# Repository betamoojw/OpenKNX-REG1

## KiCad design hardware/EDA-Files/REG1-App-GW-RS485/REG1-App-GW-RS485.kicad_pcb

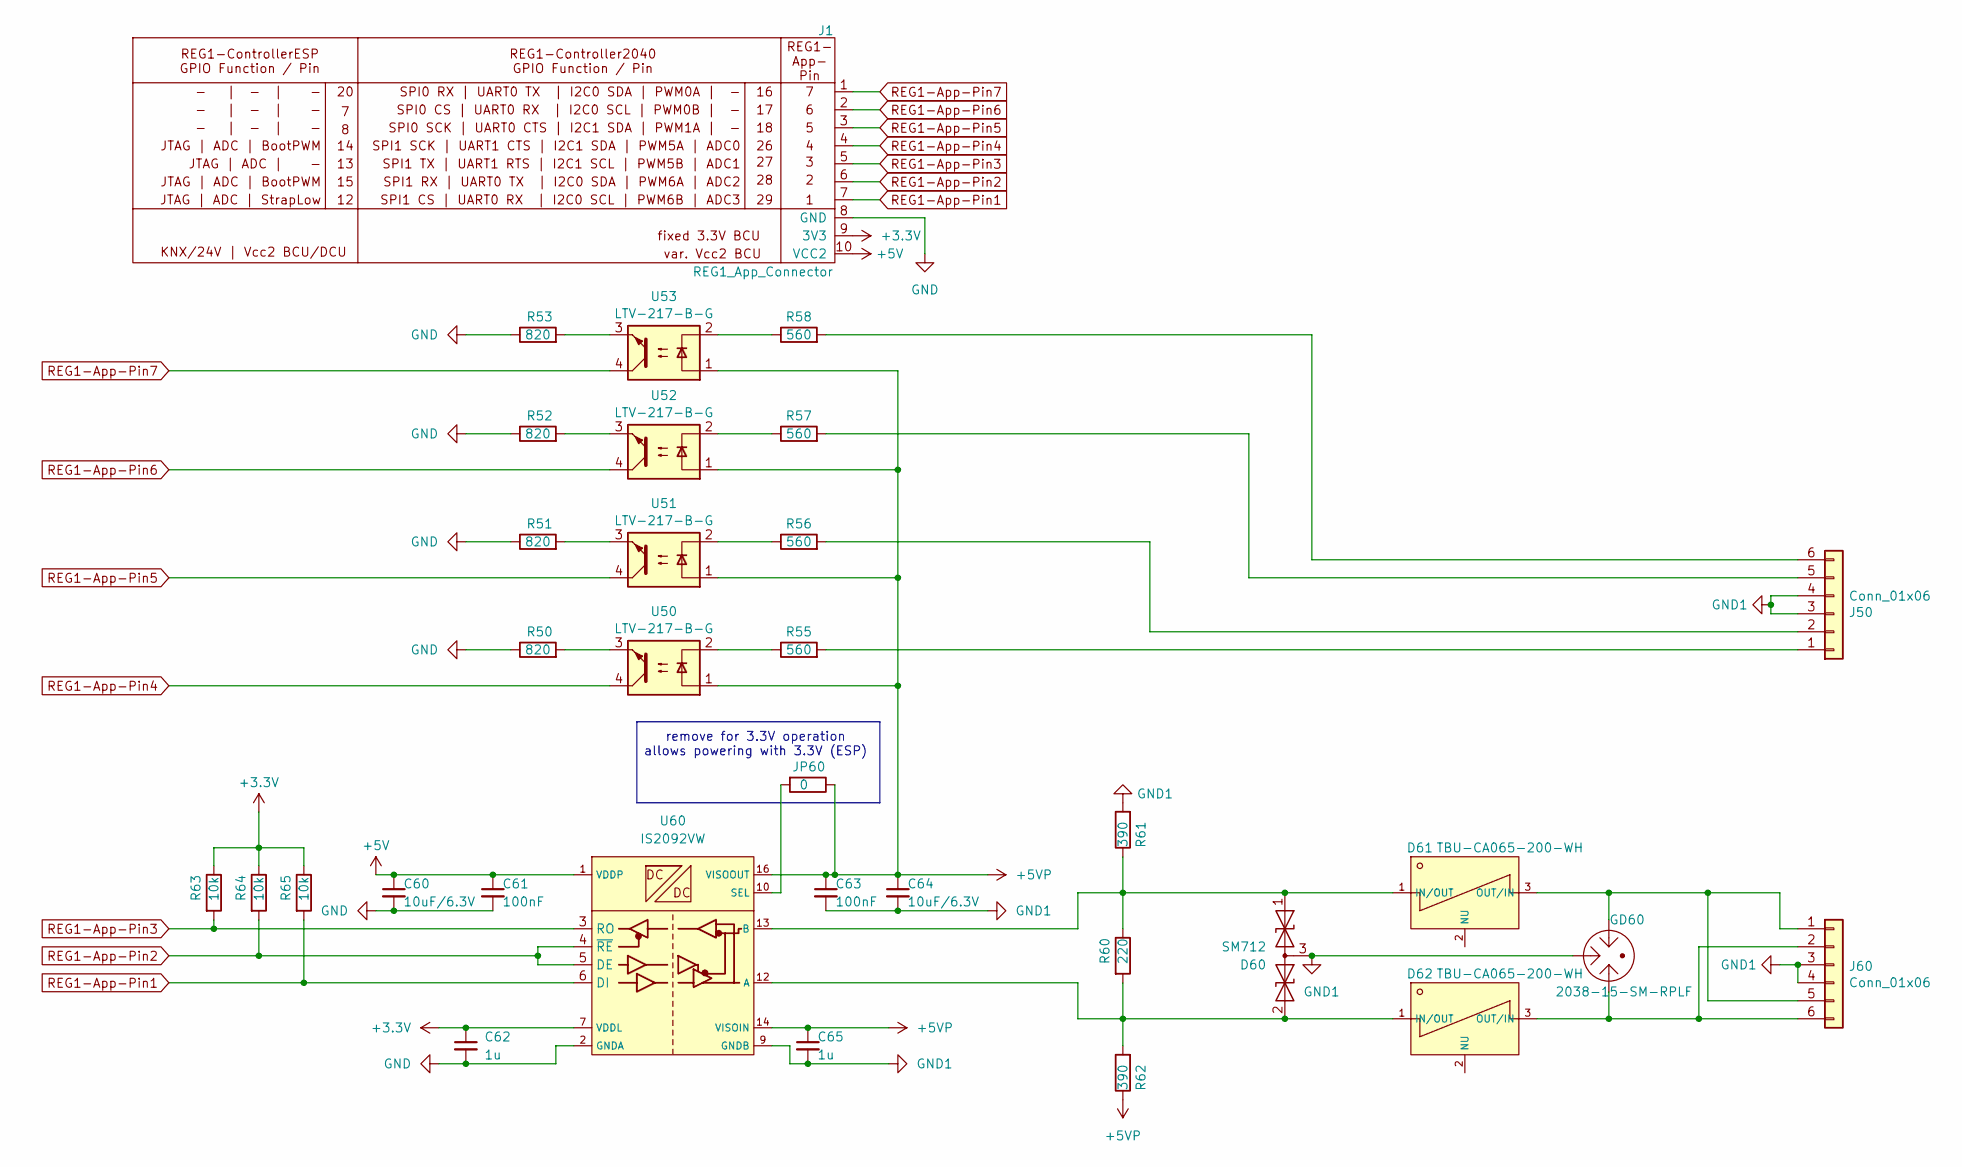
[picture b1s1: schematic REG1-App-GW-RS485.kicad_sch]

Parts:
C60, C64: 10uF/6.3V; C_0402_1005Metric
C61, C63: 100nF; C_0402_1005Metric
C62, C65: 1u; C_0402_1005Metric
D60: SM712; SOT-23
D61, D62: TBU-CA065-200-WH; DIO-SMD_3P-L6.5-W4.0-BI
GD60: 2038-15-SM-RPLF; DIO-DT-SMD-3P_L7.5-W5.0
J1: REG1_App_Connector; PinHeader_1x10_P2.54mm_Horizontal
J50, J60: Conn_01x06; PhoenixContact_MC_1,5_6-G-3.5_1x06_P3.50mm_Horizontal
JP60: 0; R_0603_1608Metric
R50, R51, R52, R53: 820; R_0603_1608Metric
R55, R56, R57, R58: 560; R_0603_1608Metric
R60: 220; R_0603_1608Metric
R61, R62: 390; R_0603_1608Metric
R63, R64, R65: 10k; R_0402_1005Metric
U50, U51, U52, U53: LTV-217-B-G; SOP-4_4.4x2.6mm_P1.27mm
U60: IS2092VW; SOIC-16W_7.5x10.3mm_P1.27mm

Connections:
+3.3V: C62.1, J1.9 (3V3), R63.1, R64.1, R65.1, U60.7 (VDDL)
+5V: C60.1, C61.1, J1.10 (VCC2), U60.1 (VDDP)
+5VP: C63.1, C64.1, C65.1, JP60.1, R62.1, U50.1, U51.1, U52.1, U53.1, U60.14 (VISOIN), U60.16 (VISOOUT)
GND: C60.2, C61.2, C62.2, J1.8 (GND), R50.1, R51.1, R52.1, R53.1, U60.2 (GNDA), U60.8 (GNDA)
GND1: C63.2, C64.2, C65.2, D60.3 (common), GD60.2, J50.3, J50.4, J60.3, J60.4, R61.2, U60.9 (GNDB), U60.15 (GNDB)
unnamed: D60.1 (A1), D61.1 (IN/OUT), R60.1, R61.1, U60.13 (B)
unnamed: D60.2 (A2), D62.1 (IN/OUT), R60.2, R62.2, U60.12 (A)
unnamed: D61.3 (OUT/IN), GD60.1, J60.1, J60.5
unnamed: D62.3 (OUT/IN), GD60.3, J60.2, J60.6
unnamed: J50.1, R55.2
unnamed: J50.2, R56.2
unnamed: J50.5, R57.2
unnamed: J50.6, R58.2
unnamed: R50.2, U50.3
unnamed: R51.2, U51.3
unnamed: R52.2, U52.3
unnamed: R53.2, U53.3
unnamed: R55.1, U50.2
unnamed: R56.1, U51.2
unnamed: R57.1, U52.2
unnamed: R58.1, U53.2
unnamed: JP60.2, U60.10 (SEL)
REG1-App-Pin1: J1.7, R65.2, U60.6 (DI)
REG1-App-Pin2: J1.6, R64.2, U60.4 (~RE), U60.5 (DE)
REG1-App-Pin3: J1.5, R63.2, U60.3 (RO)
REG1-App-Pin4: J1.4, U50.4
REG1-App-Pin5: J1.3, U51.4
REG1-App-Pin6: J1.2, U52.4
REG1-App-Pin7: J1.1, U53.4

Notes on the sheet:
remove for 3.3V operation allows powering with 3.3V (ESP)

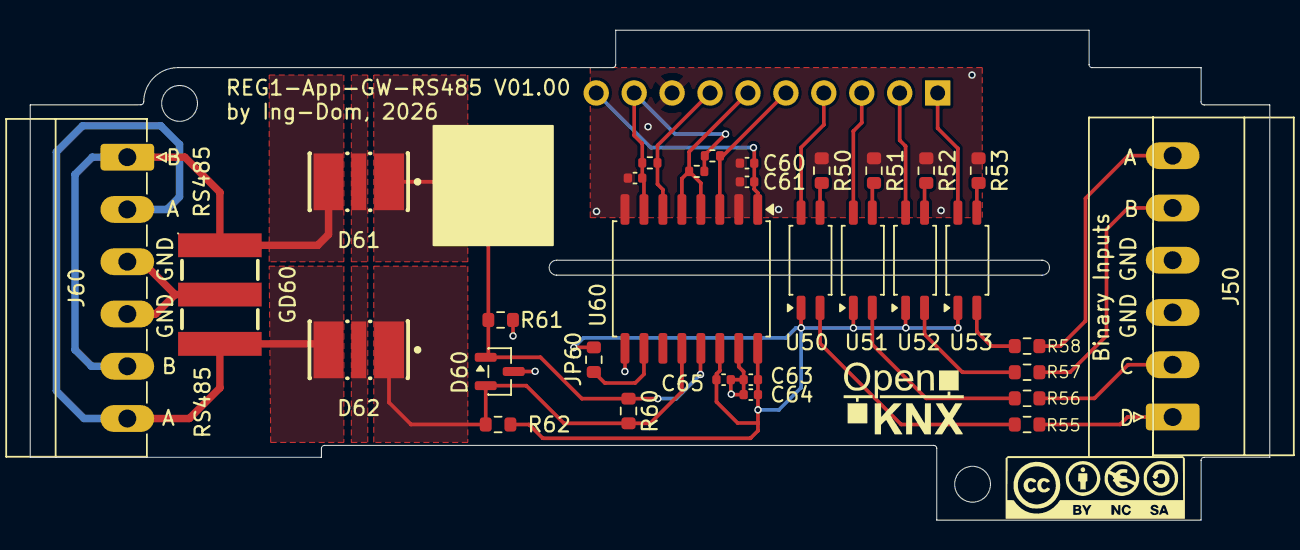
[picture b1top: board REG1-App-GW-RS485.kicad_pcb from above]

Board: 2 copper layers, 83.0 x 32.8 mm, 35 parts (1 on the bottom side), 29 nets.

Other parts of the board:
G*: LOGO; CC-BY-NY-SA_12x4
G*#2: LOGO; OpenKNX_Logo_10x10

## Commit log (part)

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2026-05-04 REG1-App-GW-RS485 V01.00

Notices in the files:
hardware/EDA-Files/REG1-App-GW-RS485/REG1-App-GW-RS485.kicad_sch:
OpenKNX Open Hardware under CC BY-NC-SA 4.0
